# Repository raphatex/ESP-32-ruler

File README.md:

# ESP-32-ruler
PCB ruler featuring an ESP-32 module, push-buttons and an OLED screen

Tetris on the Ruler

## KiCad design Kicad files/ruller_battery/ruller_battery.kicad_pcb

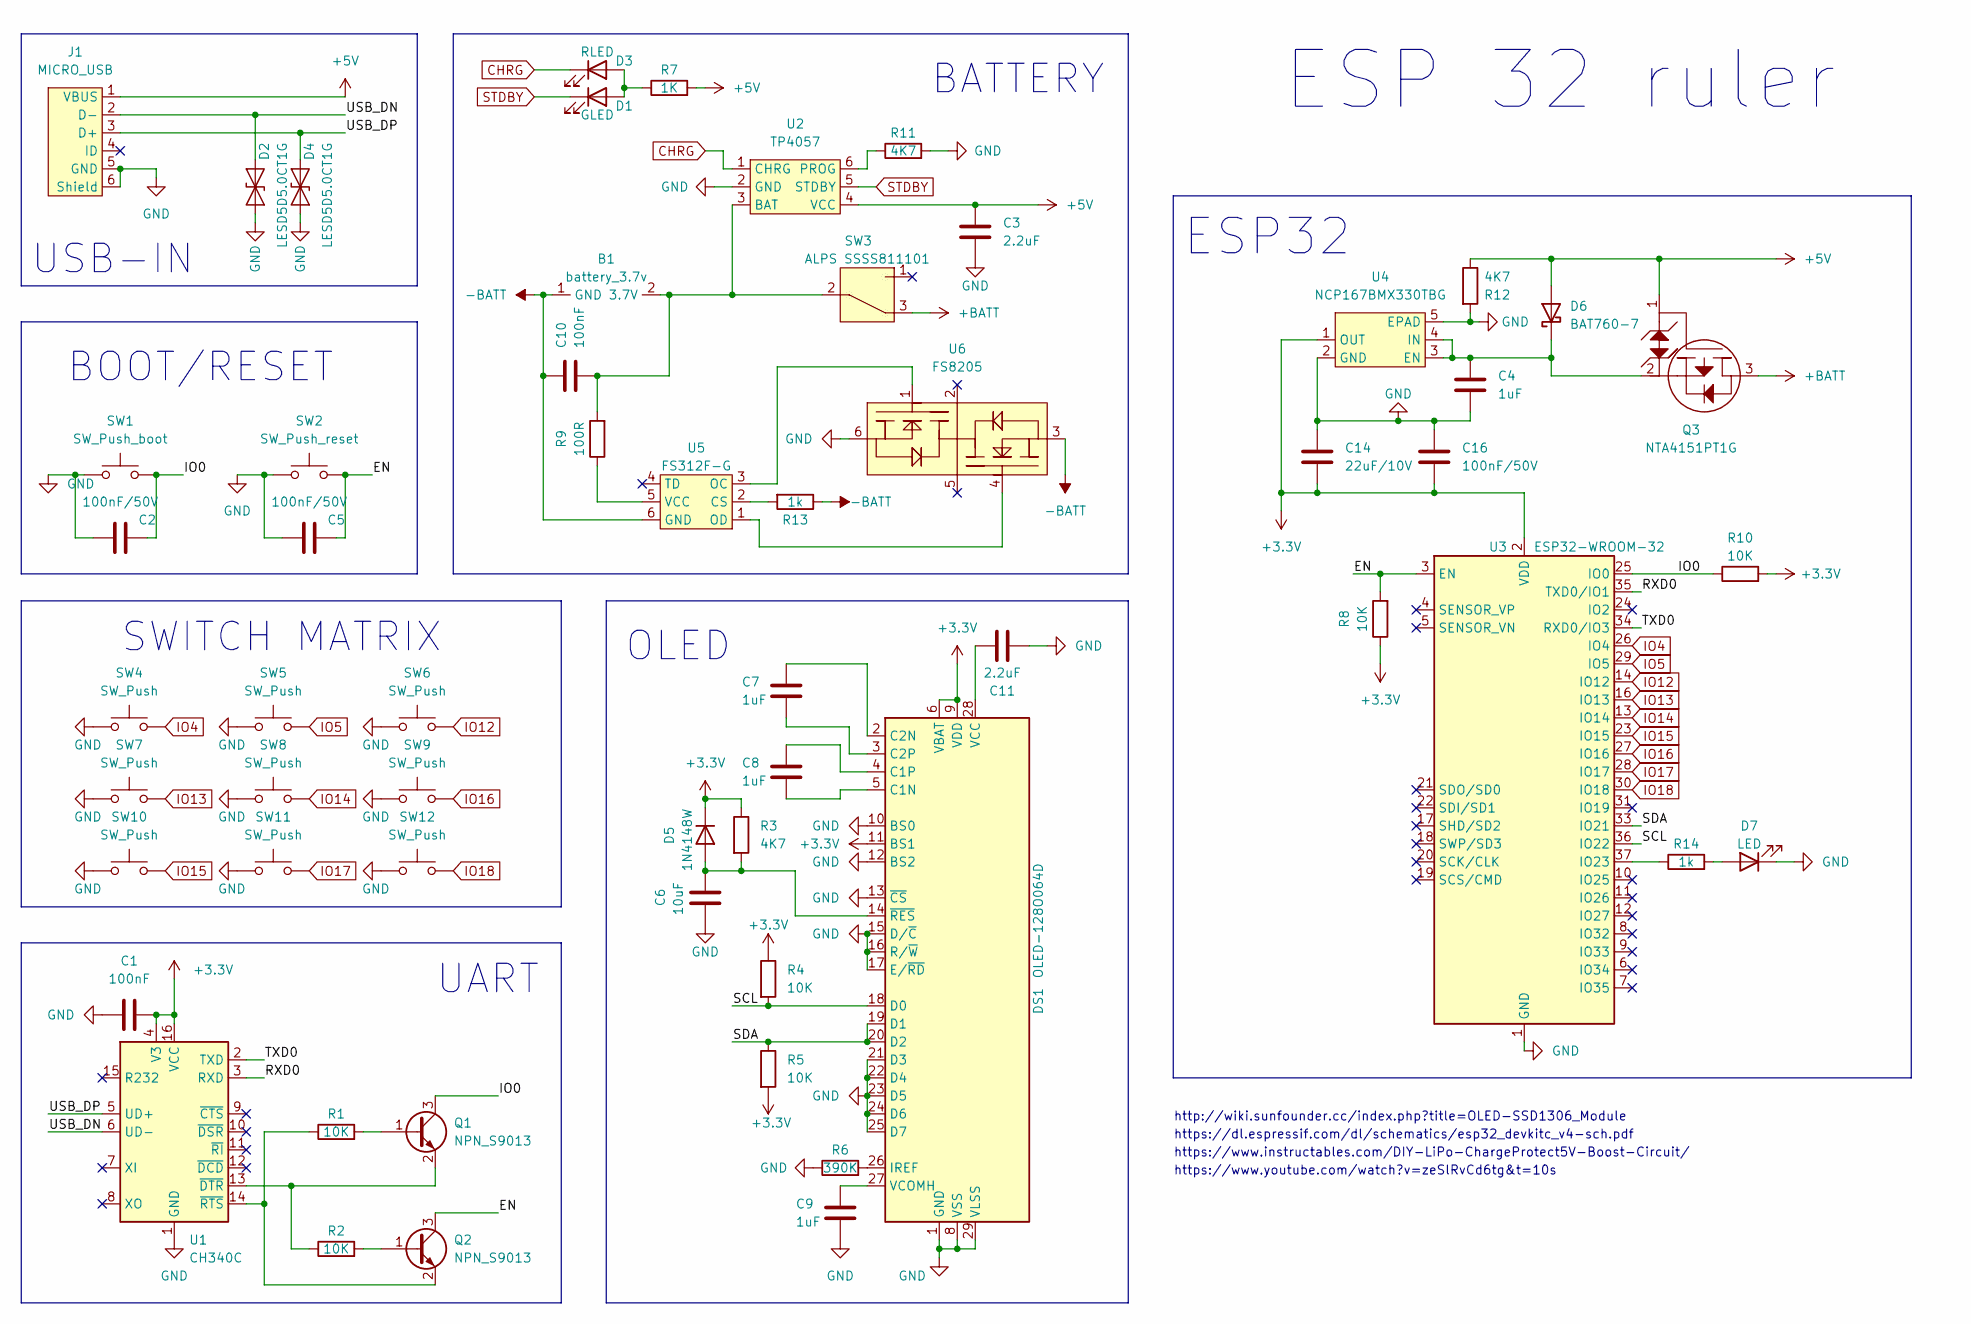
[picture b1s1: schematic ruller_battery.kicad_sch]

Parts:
B1: battery_3.7v; battery 3.7v
C1, C10: 100nF; C_0603_1608Metric_Pad1.08x0.95mm_HandSolder
C2, C5, C16: 100nF/50V; C_0603_1608Metric_Pad1.08x0.95mm_HandSolder
C3, C11: 2.2uF; C_0603_1608Metric_Pad1.08x0.95mm_HandSolder
C4, C7, C8, C9: 1uF; C_0603_1608Metric_Pad1.08x0.95mm_HandSolder
C6: 10uF; C_0603_1608Metric_Pad1.08x0.95mm_HandSolder
C14: 22uF/10V; C_0805_2012Metric
D1: RLED; LED_0603_1608Metric_Pad1.05x0.95mm_HandSolder
D2, D4: LESD5D5.0CT1G; D_SOD-523
D3: GLED; LED_0603_1608Metric_Pad1.05x0.95mm_HandSolder
D5: 1N4148W; D_SOD-123
D6: BAT760-7; D_SOD-323_HandSoldering
D7: LED; LED_0603_1608Metric_Pad1.05x0.95mm_HandSolder
DS1: OLED-128O064D
J1: MICRO_USB; MICRO USB
Q1, Q2: NPN_S9013; SOT-23
Q3: NTA4151PT1G; SOT-416
R1, R2, R4, R5, R8, R10: 10K; R_0603_1608Metric_Pad0.98x0.95mm_HandSolder
R3, R11, R12: 4K7; R_0603_1608Metric_Pad0.98x0.95mm_HandSolder
R6: 390K; R_0603_1608Metric_Pad0.98x0.95mm_HandSolder
R7: 1K; R_0603_1608Metric_Pad0.98x0.95mm_HandSolder
R9: 100R; R_0603_1608Metric_Pad0.98x0.95mm_HandSolder
R13, R14: 1k; R_0603_1608Metric_Pad0.98x0.95mm_HandSolder
SW1: SW_Push_boot; SW_SPST_TL3342
SW2: SW_Push_reset; SW_SPST_TL3342
SW3: ALPS SSSS811101; SW7_6.7X4.1MM_SM SSSS811101
SW4, SW5, SW6, SW7, SW8, SW9, SW10, SW11, SW12: SW_Push; SW_SPST_TL3342
U1: CH340C; SOIC-16_3.9x9.9mm_P1.27mm
U2: TP4057; SOT-23-6_Handsoldering
U3: ESP32-WROOM-32
U4: NCP167BMX330TBG; OnSemi_XDFN4-1EP_1.0x1.0mm_EP0.52x0.52mm
U5: FS312F-G
U6: FS8205

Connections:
+3.3V: C1.2, C14.1, C16.2, D5.1 (K), DS1.6 (VBAT), DS1.9 (VDD), DS1.11 (BS1), R3.1, R4.1, R5.2, R8.1, R10.2, U1.4 (V3), U1.16 (VCC), U3.2 (VDD), U4.1 (OUT)
+5V: C3.1, D6.2 (A), J1.1 (VBUS), Q3.1, R7.2, R12.1, U2.4 (VCC); also elsewhere on the board
+BATT: Q3.3, SW3.3
/EN: C5.2, Q2.3 (C), R8.2, SW2.2, U3.3 (EN); also elsewhere on the board
/IO0: C2.2, Q1.3 (C), R10.1, SW1.2, U3.25 (IO0)
/RXD0: U1.3 (RXD), U3.35 (TXD0/IO1)
/SCL: DS1.18 (D0), R4.2, U3.36 (IO22)
/SDA: DS1.19 (D1), DS1.20 (D2), R5.1, U3.33 (IO21)
/TXD0: U1.2 (TXD), U3.34 (RXD0/IO3)
/USB_DN: D2.2 (A2), J1.2 (D-), U1.6 (UD-)
/USB_DP: D4.2 (A2), J1.3 (D+), U1.5 (UD+)
CHRG: D1.1 (K), U2.1 (CHRG)
IO4: SW4.2, U3.26 (IO4)
IO5: SW5.2, U3.29 (IO5)
IO12: SW6.2, U3.14 (IO12)
IO13: SW7.2, U3.16 (IO13)
IO14: SW8.2, U3.13 (IO14)
IO15: SW10.2, U3.23 (IO15)
IO16: SW9.2, U3.27 (IO16)
IO17: SW11.2, U3.28 (IO17)
IO18: SW12.2, U3.30 (IO18)
unnamed: C6.1, D5.2 (A), DS1.14 (~RES), R3.2
unnamed: C7.1, DS1.2 (C2N)
unnamed: C7.2, DS1.3 (C2P)
unnamed: C8.1, DS1.4 (C1P)
unnamed: C8.2, DS1.5 (C1N)
unnamed: C9.1, DS1.27 (VCOMH)
unnamed: C11.1, DS1.28 (VCC)
unnamed: D1.2 (A), D3.2 (A), R7.1
unnamed: DS1.26 (IREF), R6.2
unnamed: Q1.1 (B), R1.2
unnamed: Q1.2 (E), R2.1, U1.13 (~DTR)
unnamed: Q2.1 (B), R2.2
unnamed: Q2.2 (E), R1.1, U1.14 (~RTS)
unnamed: C4.1, D6.1 (K), Q3.2, U4.3 (EN), U4.4 (IN)
unnamed: R9.1, R14.1, U3.37 (IO23), U5.5 (VCC)
unnamed: R11.1, U2.6 (PROG)
unnamed: R13.2, U5.2 (CS)
unnamed: U5.1 (OD), U6.4
unnamed: U5.3 (OC), U6.1
STDBY: D3.1 (K), U2.5 (STDBY)

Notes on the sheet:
https://www.youtube.com/watch?v=zeSlRvCd6tg&t=10s
BATTERY
http://wiki.sunfounder.cc/index.php?title=OLED-SSD1306_Module
https://dl.espressif.com/dl/schematics/esp32_devkitc_v4-sch.pdf
BOOT/RESET
UART
https://www.instructables.com/DIY-LiPo-ChargeProtect5V-Boost-Circuit/
SWITCH MATRIX
ESP 32 ruler
ESP32
USB-IN
OLED

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
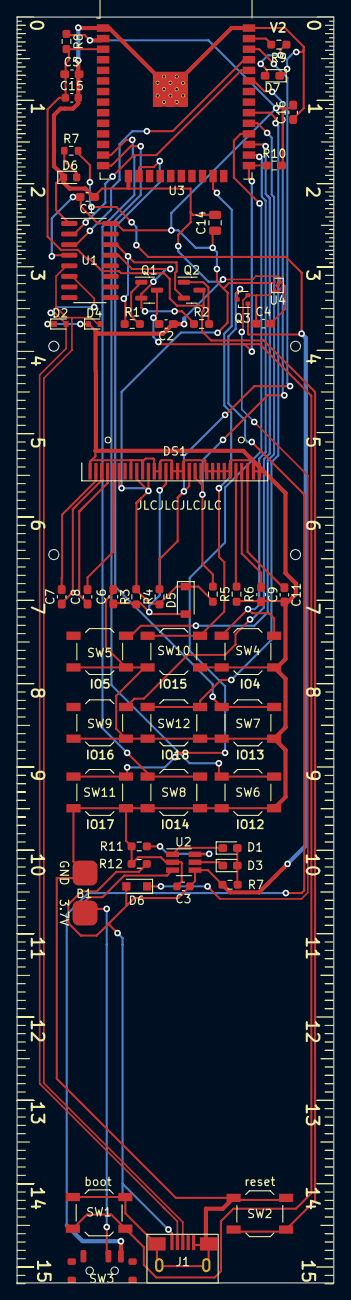
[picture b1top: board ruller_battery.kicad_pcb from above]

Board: 2 copper layers, 38.0 x 151.9 mm, 56 parts (0 on the bottom side), 42 nets.

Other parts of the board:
C15: 100nF/50V; C_0603_1608Metric
D6#2: LED; LED_0603_1608Metric
R7#2: 1k; R_0603_1608Metric

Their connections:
+5V: R7#2.2; also elsewhere on the board
/EN: C15.1; also elsewhere on the board
unnamed: D6#2.2 (A), R7#2.1

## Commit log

2024-04-11 adding photos
2024-04-11 change name
2024-07-01 zqdzq
2024-07-01 readme
2024-07-01 updating firmware
